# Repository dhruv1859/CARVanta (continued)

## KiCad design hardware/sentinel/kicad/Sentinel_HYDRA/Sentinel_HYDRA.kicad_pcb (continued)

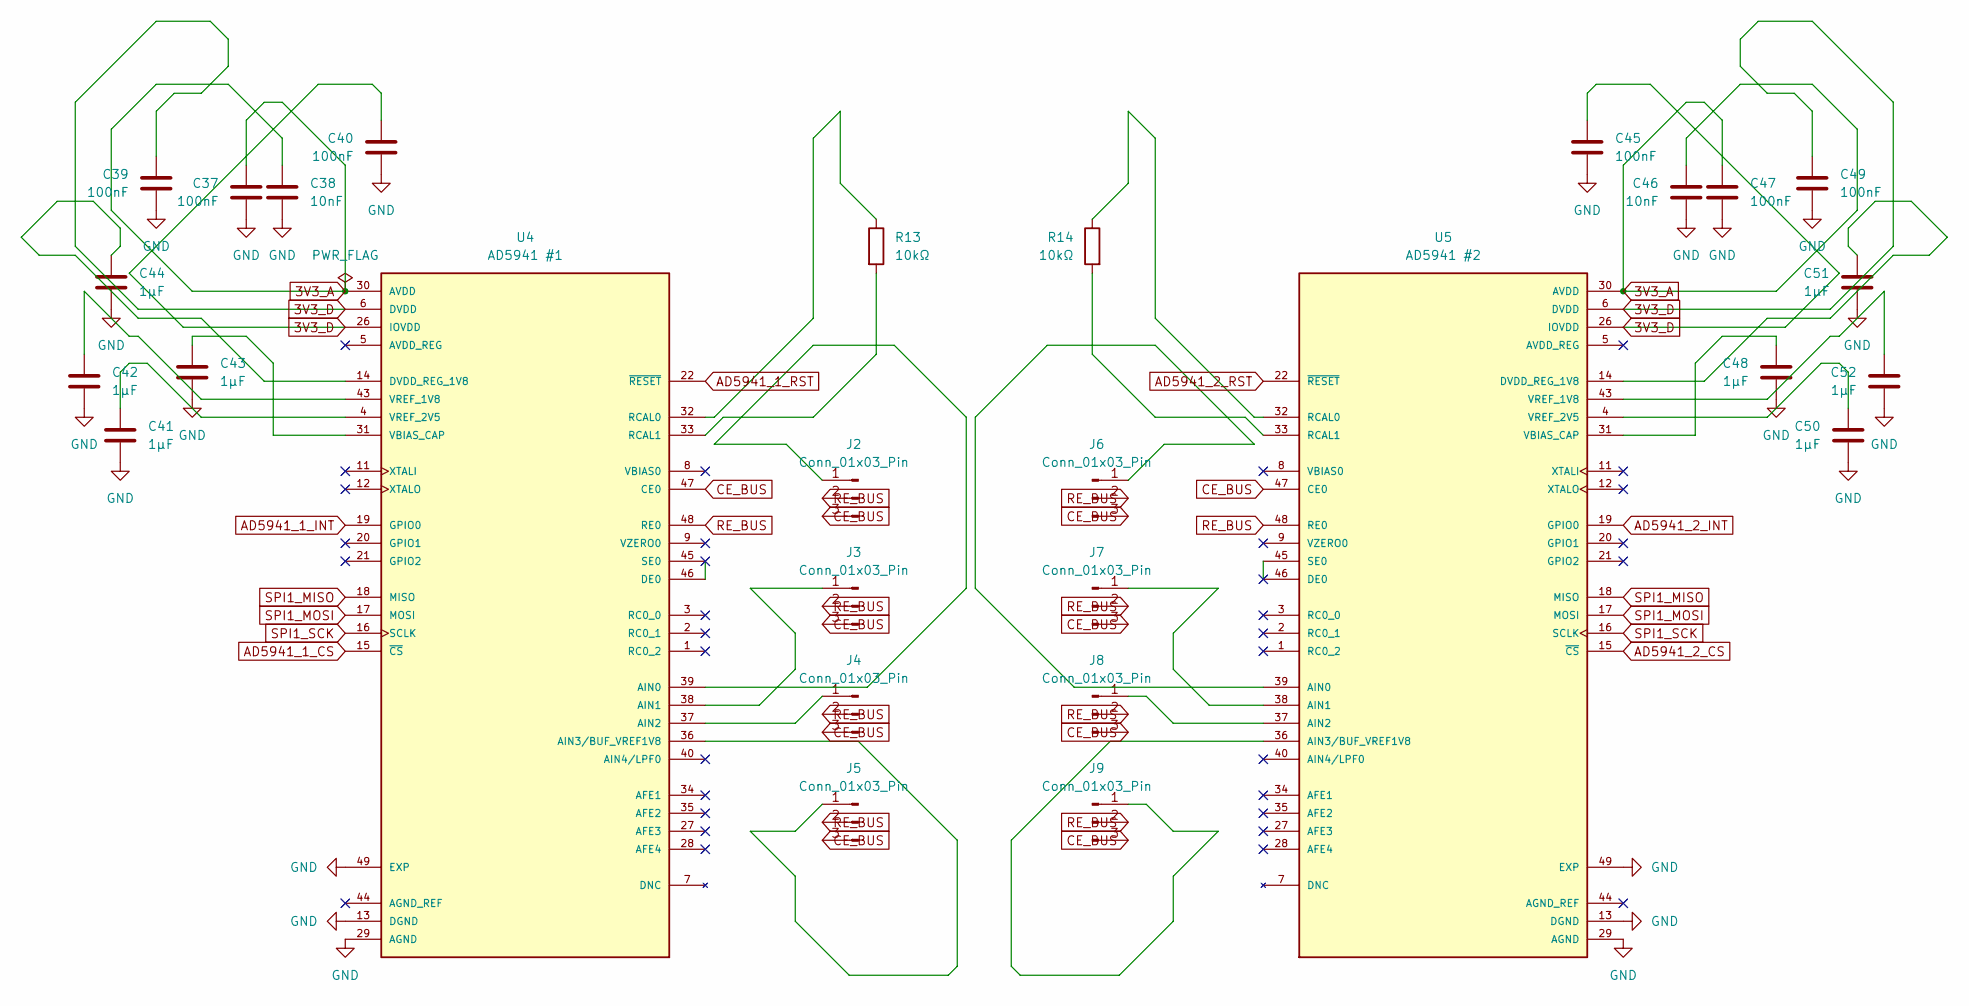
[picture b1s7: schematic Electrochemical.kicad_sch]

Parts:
C37, C39, C40, C45, C47, C49: 100nF; C_0402_1005Metric
C38, C46: 10nF; C_0402_1005Metric
C41, C42, C43, C44, C48, C50, C51, C52: 1µF; C_0402_1005Metric
J2, J3, J4, J5, J6, J7, J8, J9: Conn_01x03_Pin; Molex_PicoBlade_53047-0310_1x03_P1.25mm_Vertical
R13, R14: 10kΩ; R_0402_1005Metric
U4: AD5941 #1; QFN50P700X700X80-49N; PARTREV B
U5: AD5941 #2; QFN50P700X700X80-49N; PARTREV B

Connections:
3V3_A: C37.1, C38.1, C46.1, C47.1, U4.30 (AVDD), U4.41 (AVDD), U5.30 (AVDD), U5.41 (AVDD); also elsewhere on the board
3V3_D: C39.1, C40.1, C45.1, C49.1, U4.6 (DVDD), U4.26 (IOVDD), U5.6 (DVDD), U5.26 (IOVDD); also elsewhere on the board
+3V3: C37.2, C38.2, C39.2, C40.2, C41.2, C42.2, C43.2, C44.2, C45.2, C46.2, C47.2, C48.2, C49.2, C50.2, C51.2, C52.2, U4.13 (DGND), U4.23 (DGND), U4.25 (DGND), U4.29 (AGND), U4.42 (AGND), U4.49 (EXP), U5.13 (DGND), U5.23 (DGND), U5.25 (DGND), U5.29 (AGND), U5.42 (AGND), U5.49 (EXP); also elsewhere on the board
AD5941_1_CS: U4.15 (~CS); also elsewhere on the board
AD5941_1_INT: U4.19 (GPIO0); also elsewhere on the board
AD5941_1_RST: U4.22 (~RESET); also elsewhere on the board
AD5941_2_CS: U5.15 (~CS); also elsewhere on the board
AD5941_2_INT: U5.19 (GPIO0); also elsewhere on the board
AD5941_2_RST: U5.22 (~RESET); also elsewhere on the board
CE_BUS: J2.3, J3.3, J4.3, J5.3, J6.3, J7.3, J8.3, J9.3, U4.47 (CE0), U5.47 (CE0)
unnamed: J2.1, U4.39 (AIN0)
unnamed: J3.1, U4.38 (AIN1)
unnamed: J4.1, U4.37 (AIN2)
unnamed: J5.1, U4.36 (AIN3/BUF_VREF1V8)
unnamed: J6.1, U5.39 (AIN0)
unnamed: J7.1, U5.38 (AIN1)
unnamed: J8.1, U5.37 (AIN2)
unnamed: J9.1, U5.36 (AIN3/BUF_VREF1V8)
unnamed: C44.1, U4.14 (DVDD_REG_1V8)
unnamed: R13.1, U4.32 (RCAL0)
unnamed: R13.2, U4.33 (RCAL1)
unnamed: C43.1, U4.31 (VBIAS_CAP)
unnamed: C42.1, U4.43 (VREF_1V8)
unnamed: C41.1, U4.4 (VREF_2V5)
unnamed: C51.1, U5.14 (DVDD_REG_1V8)
unnamed: R14.1, U5.32 (RCAL0)
unnamed: R14.2, U5.33 (RCAL1)
unnamed: C48.1, U5.31 (VBIAS_CAP)
unnamed: C52.1, U5.43 (VREF_1V8)
unnamed: C50.1, U5.4 (VREF_2V5)
RE_BUS: J2.2, J3.2, J4.2, J5.2, J6.2, J7.2, J8.2, J9.2, U4.48 (RE0), U5.48 (RE0)
SPI1_MISO: U4.18 (MISO), U5.18 (MISO); also elsewhere on the board
SPI1_MOSI: U4.17 (MOSI), U5.17 (MOSI); also elsewhere on the board
SPI1_SCK: U4.16 (SCLK), U5.16 (SCLK); also elsewhere on the board

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
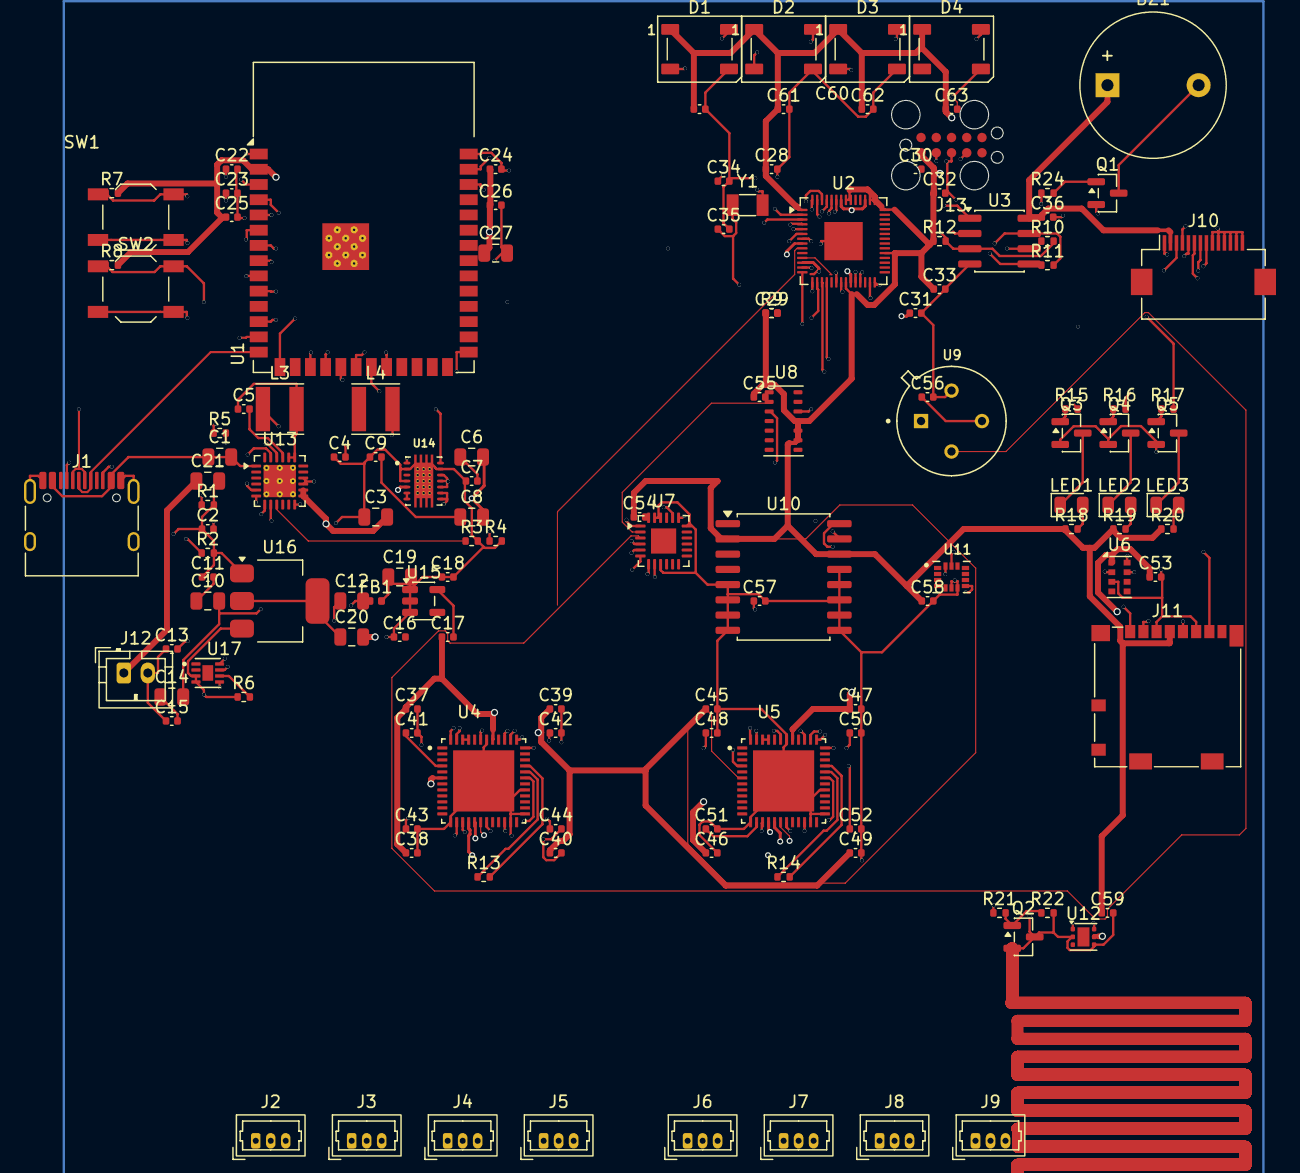
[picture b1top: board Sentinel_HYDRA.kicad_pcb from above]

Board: 6 copper layers, 135 parts (0 on the bottom side), 123 nets.

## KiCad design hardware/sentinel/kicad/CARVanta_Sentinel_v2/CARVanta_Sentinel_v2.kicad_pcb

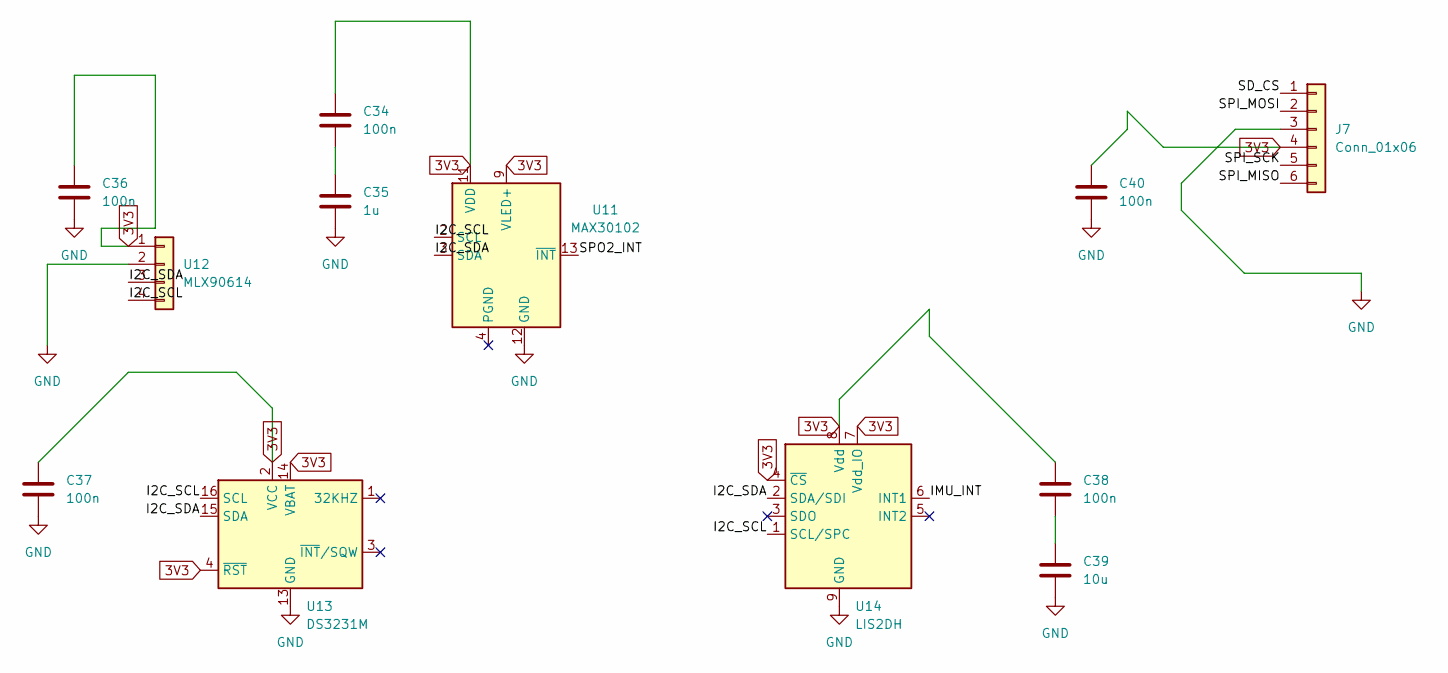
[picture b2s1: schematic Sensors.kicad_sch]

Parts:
C34, C36, C37, C38, C40: 100n; C_0805_2012Metric
C35: 1u; C_0805_2012Metric
C39: 10u; C_0805_2012Metric
J7: Conn_01x06; PinHeader_1x06_P2.54mm_Vertical
U11: MAX30102; Maxim_OLGA-14_3.3x5.6mm_P0.8mm
U12: MLX90614; TO-39-4
U13: DS3231M; SOIC-16W_7.5x10.3mm_P1.27mm
U14: LIS2DH; Bosch_LGA-14_3x2.5mm_P0.5mm

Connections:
3V3: C34.1, C35.2, C36.1, C36.2, C37.1, C37.2, C38.1, C39.2, C40.1, C40.2, J7.3, J7.4, U11.9 (VLED+), U11.10 (VLED+), U11.11 (VDD), U11.12 (GND), U12.1, U12.2, U13.2 (VCC), U13.4 (~RST), U13.5 (GND), U13.6 (GND), U13.7 (GND), U13.8 (GND), U13.9 (GND), U13.10 (GND), U13.11 (GND), U13.12 (GND), U13.13 (GND), U13.14 (VBAT), U14.4 (~CS), U14.7 (Vdd_IO), U14.8 (Vdd), U14.9 (GND), U14.10 (GND), U14.11 (GND), U14.12 (GND), U14.13 (GND), U14.14 (GND); also elsewhere on the board
/Sensors/I2C_SCL: U11.2 (SCL), U12.4, U13.16 (SCL), U14.1 (SCL/SPC)
/Sensors/I2C_SDA: U11.3 (SDA), U12.3, U13.15 (SDA), U14.2 (SDA/SDI)
/Sensors/IMU_INT: U14.6 (INT1)
/Sensors/SD_CS: J7.1
/Sensors/SPI_MISO: J7.6
/Sensors/SPI_MOSI: J7.2
/Sensors/SPI_SCK: J7.5
/Sensors/SPO2_INT: U11.13 (~INT)
unnamed: C34.2, C35.1
unnamed: C38.2, C39.1

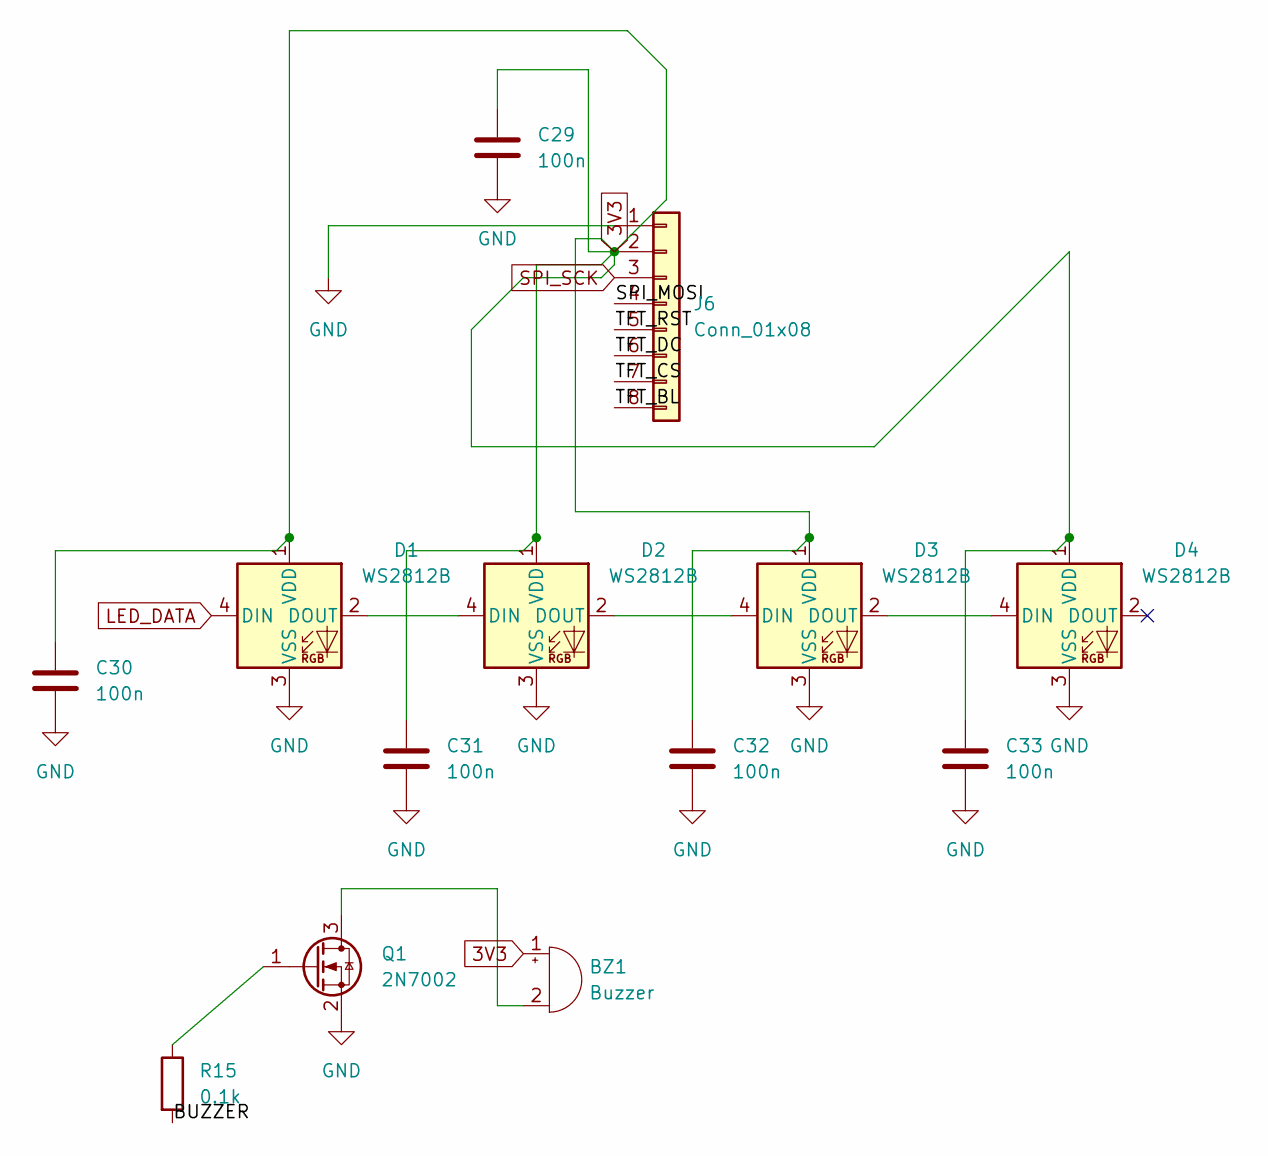
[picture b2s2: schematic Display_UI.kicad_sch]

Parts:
BZ1: Buzzer; Buzzer_12x9.5RM7.6
C29, C30, C31, C32, C33: 100n; C_0805_2012Metric
D1, D2, D3, D4: WS2812B; LED_WS2812B_PLCC4_5.0x5.0mm_P3.2mm
J6: Conn_01x08; PinHeader_1x08_P2.54mm_Vertical
Q1: 2N7002; SOT-23
R15: 0.1k; R_0402_1005Metric

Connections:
3V3: BZ1.1 (+), C29.1, C29.2, C30.1, C30.2, C31.1, C31.2, C32.1, C32.2, C33.1, C33.2, D1.1 (VDD), D1.3 (VSS), D2.1 (VDD), D2.3 (VSS), D3.1 (VDD), D3.3 (VSS), D4.1 (VDD), D4.3 (VSS), J6.1, J6.2, Q1.2 (S); also elsewhere on the board
/Display_UI/BUZZER: R15.2
/Display_UI/SPI_MOSI: J6.4
/Display_UI/TFT_BL: J6.8
/Display_UI/TFT_CS: J6.7
/Display_UI/TFT_DC: J6.6
/Display_UI/TFT_RST: J6.5
LED_DATA: D1.4 (DIN); also elsewhere on the board
unnamed: BZ1.2 (-), Q1.3 (D)
unnamed: D1.2 (DOUT), D2.4 (DIN)
unnamed: D2.2 (DOUT), D3.4 (DIN)
unnamed: D3.2 (DOUT), D4.4 (DIN)
unnamed: Q1.1 (G), R15.1
SPI_SCK: J6.3; also elsewhere on the board

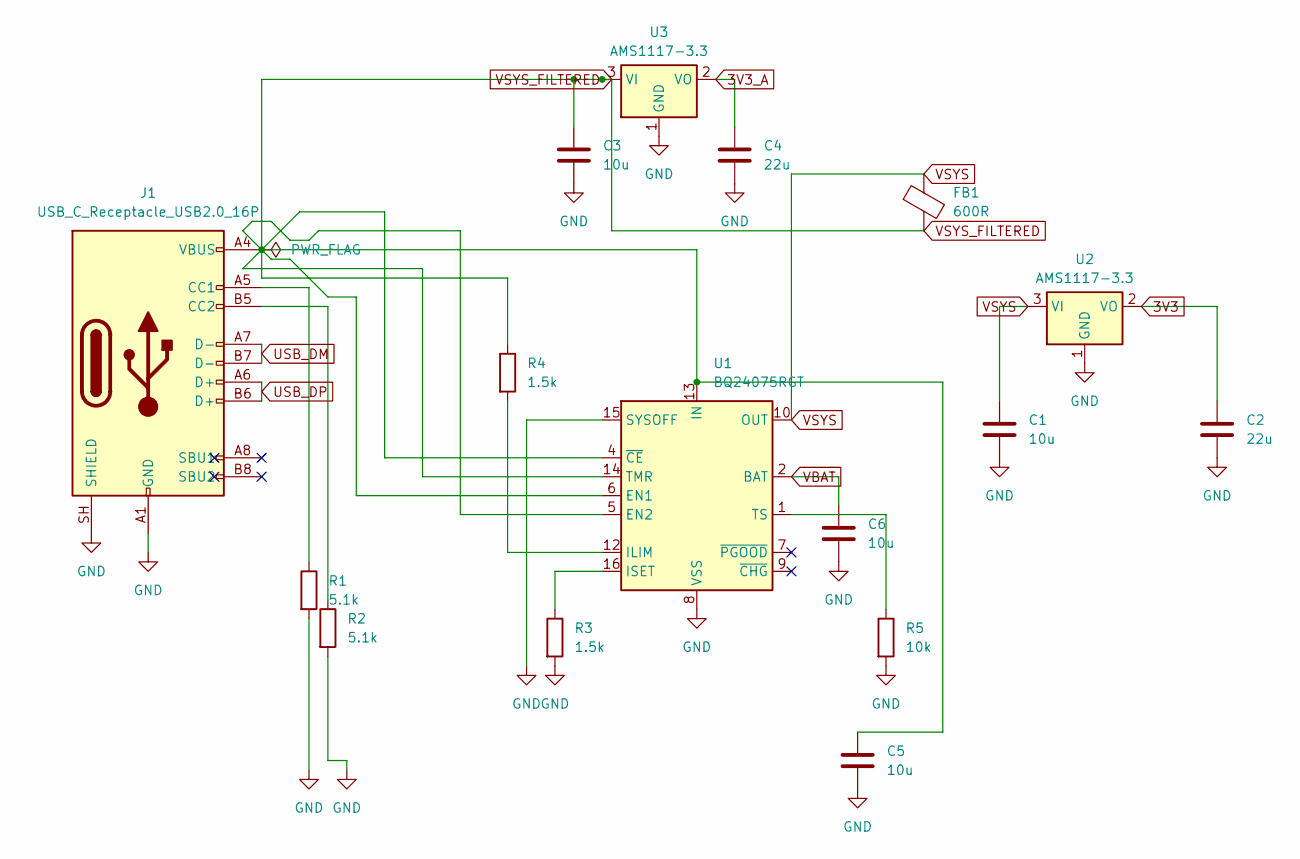
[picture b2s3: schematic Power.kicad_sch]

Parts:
C1, C3, C5, C6: 10u; C_0805_2012Metric
C2, C4: 22u; C_0805_2012Metric
FB1: 600R; L_0402_1005Metric
J1: USB_C_Receptacle_USB2.0_16P; USB_C_Receptacle_HCTL_HC-TYPE-C-16P-01A
R1, R2: 5.1k; R_0402_1005Metric
R3, R4: 1.5k; R_0402_1005Metric
R5: 10k; R_0402_1005Metric
U1: BQ24075RGT; VQFN-16-1EP_3x3mm_P0.5mm_EP1.8x1.8mm
U2, U3: AMS1117-3.3; SOT-223-3_TabPin2

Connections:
3V3: C1.2, C2.1, C2.2, C3.2, C4.2, C5.2, C6.2, J1.A1 (GND), J1.A12 (GND), J1.B1 (GND), J1.B12 (GND), J1.SH (SHIELD), R1.2, R2.2, R3.2, R5.2, U1.8 (VSS), U1.15 (SYSOFF), U1.17 (VSS), U2.1 (GND), U2.2 (VO), U3.1 (GND); also elsewhere on the board
3V3_A: C4.1, U3.2 (VO); also elsewhere on the board
unnamed: J1.A5 (CC1), R1.1
unnamed: J1.B5 (CC2), R2.1
unnamed: R4.2, U1.12 (ILIM)
unnamed: R3.1, U1.16 (ISET)
unnamed: R5.1, U1.1 (TS)
USB_DM: J1.A7 (D-), J1.B7 (D-); also elsewhere on the board
USB_DP: J1.A6 (D+), J1.B6 (D+); also elsewhere on the board
VBAT: C6.1, U1.2 (BAT), U1.3 (BAT); also elsewhere on the board
VSYS: C1.1, FB1.1, U1.10 (OUT), U1.11 (OUT), U2.3 (VI)
VSYS_FILTERED: C3.1, C5.1, FB1.2, J1.A4 (VBUS), J1.A9 (VBUS), J1.B4 (VBUS), J1.B9 (VBUS), R4.1, U1.4 (~CE), U1.5 (EN2), U1.6 (EN1), U1.13 (IN), U1.14 (TMR), U3.3 (VI)

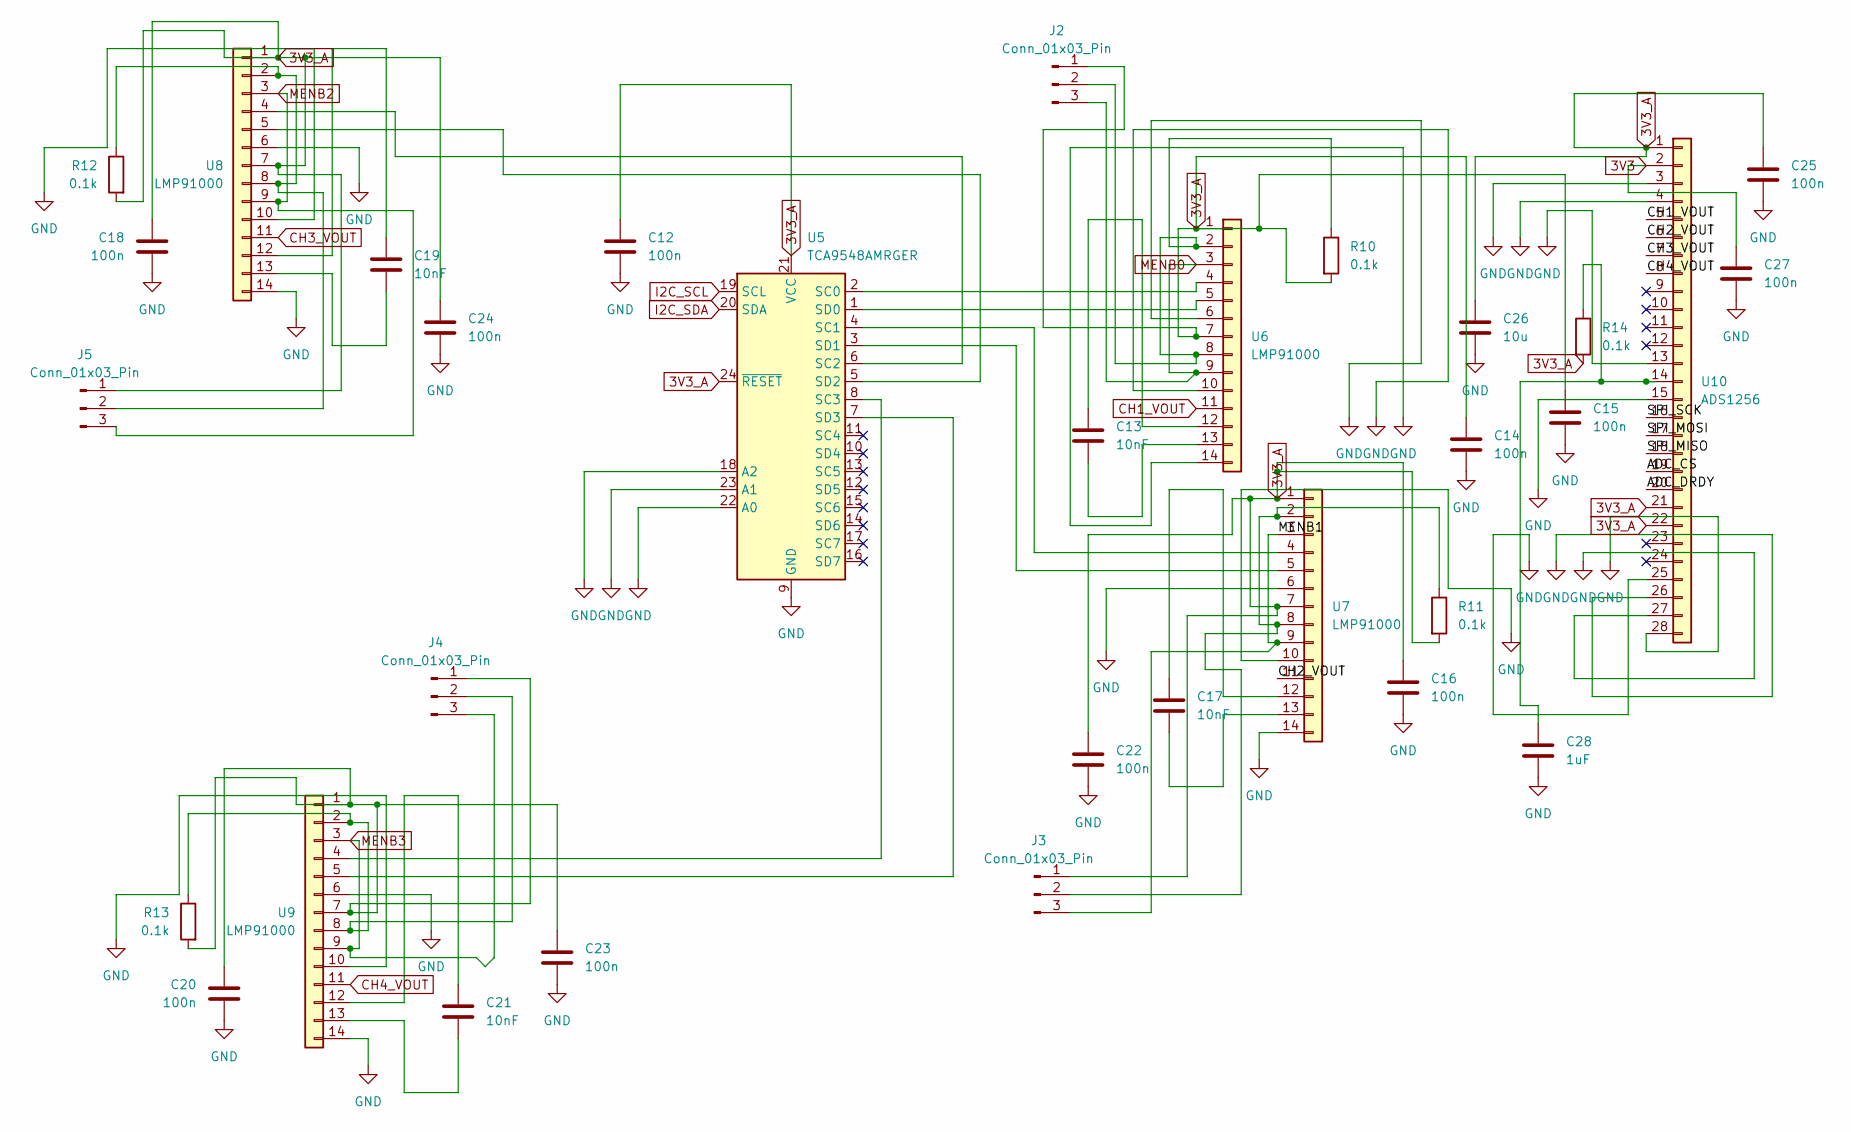
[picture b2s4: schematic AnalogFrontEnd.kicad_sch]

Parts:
C12, C14, C15, C16, C18, C20, C22, C23, C24, C25, C27: 100n; C_0805_2012Metric
C13, C17, C19, C21: 10nF; C_0805_2012Metric
C26: 10u; C_0805_2012Metric
C28: 1uF; C_0805_2012Metric
J2, J3, J4, J5: Conn_01x03_Pin; PinHeader_1x03_P2.54mm_Vertical
R10, R11, R12, R13, R14: 0.1k; R_0402_1005Metric
U5: TCA9548AMRGER; TSSOP-24_4.4x7.8mm_P0.65mm
U6, U7, U8, U9: LMP91000; TSSOP-14_4.4x5mm_P0.65mm
U10: ADS1256; TSSOP-28_4.4x9.7mm_P0.65mm

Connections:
3V3: C12.2, C14.2, C15.2, C16.2, C18.2, C20.2, C22.2, C23.2, C24.2, C25.2, C26.2, C27.1, C27.2, C28.2, U5.9 (GND), U5.18 (A2), U5.22 (A0), U5.23 (A1), U6.6, U6.10, U6.14, U7.6, U7.10, U7.14, U8.6, U8.10, U8.14, U9.6, U9.10, U9.14, U10.2, U10.3, U10.4, U10.13, U10.15, U10.25, U10.26, U10.27, U10.28; also elsewhere on the board
3V3_A: C12.1, C14.1, C15.1, C16.1, C18.1, C22.1, C24.1, C25.1, C26.1, J2.1, J3.1, J5.1, R10.2, R11.2, R12.2, R14.2, U5.21 (VCC), U5.24 (~RESET), U6.1, U6.7, U7.1, U7.7, U8.1, U8.7, U10.1, U10.21, U10.22; also elsewhere on the board
/AnalogFrontEnd/ADC_CS: U10.19
/AnalogFrontEnd/ADC_DRDY: U10.20
/AnalogFrontEnd/CH2_VOUT: U7.11, U10.6
/AnalogFrontEnd/MENB1: J3.3, U7.3, U7.9
/AnalogFrontEnd/SPI_MISO: U10.18
/AnalogFrontEnd/SPI_MOSI: U10.17
/AnalogFrontEnd/SPI_SCK: U10.16
CH1_VOUT: U6.11, U10.5
CH3_VOUT: U8.11, U10.7
CH4_VOUT: U9.11, U10.8
I2C_SCL: U5.19 (SCL); also elsewhere on the board
I2C_SDA: U5.20 (SDA); also elsewhere on the board
MENB0: J2.3, U6.3, U6.9; also elsewhere on the board
MENB2: J5.3, U8.3, U8.9; also elsewhere on the board
MENB3: J4.3, U9.3, U9.9; also elsewhere on the board
unnamed: J2.2, R10.1, U6.2, U6.8
unnamed: J3.2, R11.1, U7.2, U7.8
unnamed: C20.1, C23.1, J4.1, R13.2, U9.1, U9.7
unnamed: J4.2, R13.1, U9.2, U9.8
unnamed: J5.2, R12.1, U8.2, U8.8
unnamed: U5.2 (SC0), U6.4
unnamed: U5.4 (SC1), U7.4
unnamed: U5.6 (SC2), U8.4
unnamed: U5.8 (SC3), U9.4
unnamed: U5.1 (SD0), U6.5
unnamed: U5.3 (SD1), U7.5
unnamed: U5.5 (SD2), U8.5
unnamed: U5.7 (SD3), U9.5
unnamed: C13.1, U6.12
unnamed: C13.2, U6.13
unnamed: C17.1, U7.12
unnamed: C17.2, U7.13
unnamed: C19.1, U8.12
unnamed: C19.2, U8.13
unnamed: C21.1, U9.12
unnamed: C21.2, U9.13
unnamed: C28.1, R14.1, U10.14

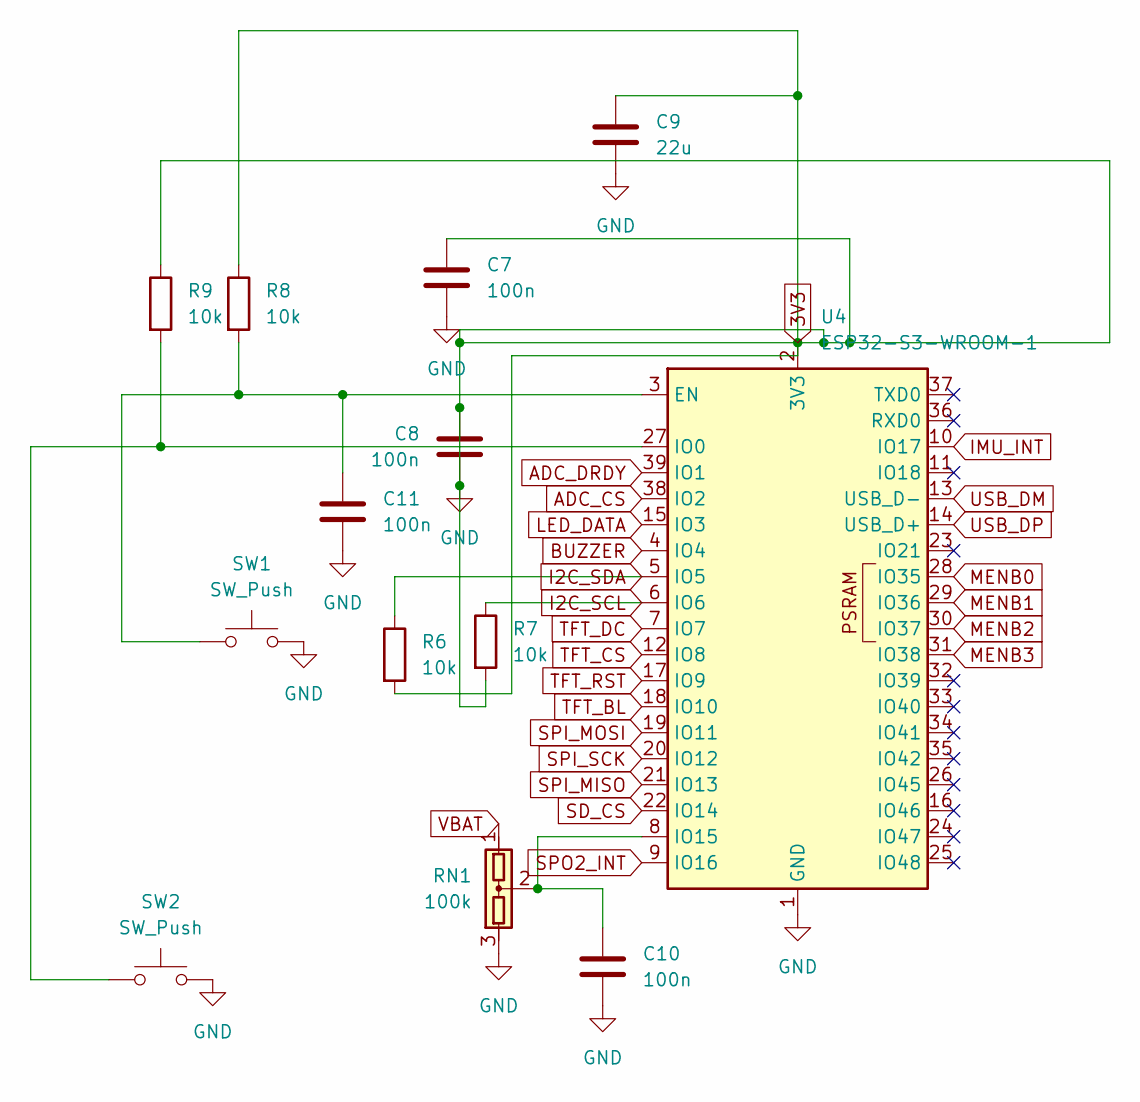
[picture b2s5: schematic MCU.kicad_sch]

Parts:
C7, C8, C10, C11: 100n; C_0805_2012Metric
C9: 22u; C_0805_2012Metric
R6, R7, R8, R9: 10k; R_0402_1005Metric
RN1: 100k; R_Array_Convex_2x0402
SW1, SW2: SW_Push; SW_SPST_PTS645Sx43SMTR92
U4: ESP32-S3-WROOM-1

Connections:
3V3: C7.1, C7.2, C8.1, C8.2, C9.1, C9.2, C10.2, C11.2, R6.2, R7.2, R8.1, R9.1, RN1.3, SW1.2, SW2.2, U4.1 (GND), U4.2 (3V3), U4.40 (GND), U4.41 (GND); also elsewhere on the board
ADC_CS: U4.38 (IO2)
ADC_DRDY: U4.39 (IO1)
BUZZER: U4.4 (IO4)
I2C_SCL: R7.1, U4.6 (IO6); also elsewhere on the board
I2C_SDA: R6.1, U4.5 (IO5); also elsewhere on the board
IMU_INT: U4.10 (IO17)
LED_DATA: U4.15 (IO3); also elsewhere on the board
MENB0: U4.28 (IO35); also elsewhere on the board
MENB1: U4.29 (IO36)
MENB2: U4.30 (IO37); also elsewhere on the board
MENB3: U4.31 (IO38); also elsewhere on the board
unnamed: C11.1, R8.2, SW1.1, U4.3 (EN)
unnamed: R9.2, SW2.1, U4.27 (IO0)
unnamed: C10.1, RN1.2, U4.8 (IO15)
SD_CS: U4.22 (IO14)
SPI_MISO: U4.21 (IO13)
SPI_MOSI: U4.19 (IO11)
SPI_SCK: U4.20 (IO12); also elsewhere on the board
SPO2_INT: U4.9 (IO16)
TFT_BL: U4.18 (IO10)
TFT_CS: U4.12 (IO8)
TFT_DC: U4.7 (IO7)
TFT_RST: U4.17 (IO9)
USB_DM: U4.13 (USB_D-); also elsewhere on the board
USB_DP: U4.14 (USB_D+); also elsewhere on the board
VBAT: RN1.1; also elsewhere on the board

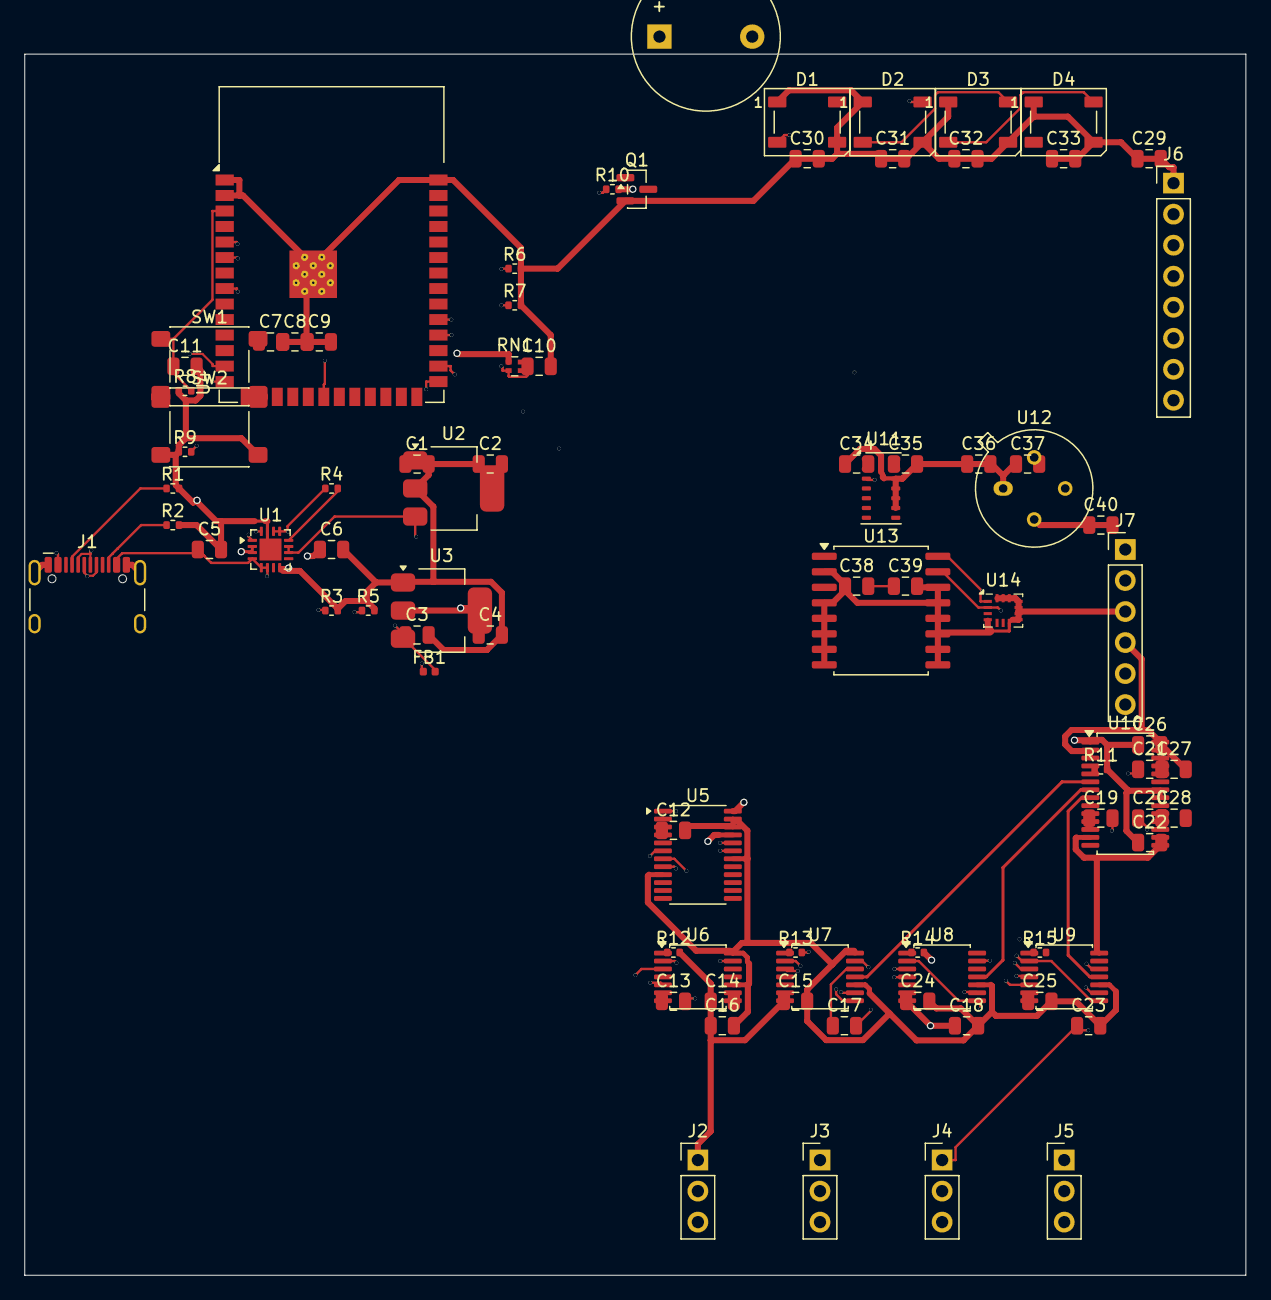
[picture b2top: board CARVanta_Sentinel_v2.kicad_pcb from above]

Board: 6 copper layers, 100.0 x 100.0 mm, 86 parts (0 on the bottom side), 58 nets.

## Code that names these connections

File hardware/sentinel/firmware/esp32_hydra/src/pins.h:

/*
 * CARVanta Sentinel HYDRA — ESP32-S3 Pin Definitions
 * Matches KiCad schematic: HYDRA_WALKTHROUGH_PART1.md
 * Sheet 2: ESP32 Pin Map
 */

#pragma once

// ─── UART to RP2040 ──────────────────────────────────────
#define PIN_UART_TX         1   // GPIO1 → RP2040 GPIO0 (RX)
#define PIN_UART_RX         2   // GPIO2 ← RP2040 GPIO1 (TX)

// ─── I2C Main Bus (→ TCA9548A Mux) ──────────────────────
#define PIN_I2C_SDA         5   // GPIO5
#define PIN_I2C_SCL         6   // GPIO6

// ─── SPI0 (TFT Display + SD Card) ───────────────────────
#define PIN_SPI0_MOSI       11  // GPIO11
#define PIN_SPI0_SCK        12  // GPIO12
#define PIN_SPI0_MISO       13  // GPIO13
#define PIN_TFT_CS          8   // GPIO8
#define PIN_TFT_DC          7   // GPIO7
#define PIN_TFT_RST         9   // GPIO9
#define PIN_TFT_BL          10  // GPIO10
#define PIN_SD_CS           14  // GPIO14

// ─── UI: LEDs + Buzzer ──────────────────────────────────
#define PIN_LED_DATA        3   // GPIO3 → WS2812B D1 DIN
#define PIN_BUZZER          4   // GPIO4 → Q1 gate (buzzer driver)
#define NUM_WS2812B_LEDS    4   // D1–D4

// ─── Status Inputs ──────────────────────────────────────
#define PIN_CHG_INT         15  // GPIO15 ← BQ25895 INT (charge status)
#define PIN_BATT_ALT        16  // GPIO16 ← MAX17048 ALT (low battery)
#define PIN_PG_3V3          17  // GPIO17 ← TPS63020 PG (power good)

// ─── USB (Hardware-fixed, cannot remap) ──────────────────
#define PIN_USB_DM          19  // GPIO19 — USB D−
#define PIN_USB_DP          20  // GPIO20 — USB D+

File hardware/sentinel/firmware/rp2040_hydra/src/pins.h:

/*
 * CARVanta Sentinel HYDRA — RP2040 Pin Definitions
 * Matches KiCad schematic: HYDRA_WALKTHROUGH_PART1.md
 * Sheet 3: RP2040 Pin Map
 */

#pragma once

// ─── UART to ESP32 ───────────────────────────────────────
#define PIN_UART_RX         0   // GPIO0 ← ESP32 GPIO1 (TX)
#define PIN_UART_TX         1   // GPIO1 → ESP32 GPIO2 (RX)

// ─── SPI1 — AD5941 Bus ──────────────────────────────────
#define PIN_SPI1_SCK        6   // GPIO6
#define PIN_SPI1_MOSI       7   // GPIO7
#define PIN_SPI1_MISO       8   // GPIO8
#define PIN_AD5941_1_CS     2   // GPIO2  — AFE #1 chip select
#define PIN_AD5941_1_RST    3   // GPIO3  — AFE #1 reset
#define PIN_AD5941_2_CS     4   // GPIO4  — AFE #2 chip select
#define PIN_AD5941_2_RST    5   // GPIO5  — AFE #2 reset
#define PIN_AD5941_1_INT    9   // GPIO9  — AFE #1 interrupt
#define PIN_AD5941_2_INT    10  // GPIO10 — AFE #2 interrupt

// ─── I2C1 — AS7341 + TMP117 ────────────────────────────
#define PIN_I2C1_SDA        12  // GPIO12  (Wire1)
#define PIN_I2C1_SCL        13  // GPIO13  (Wire1)

// ─── Heater PWM ─────────────────────────────────────────
#define PIN_HEATER_PWM      14  // GPIO14 → AO3400 gate

// ─── Excitation LEDs ────────────────────────────────────
#define PIN_UV_LED_EN       15  // GPIO15 → Q3 gate (UV 365nm)
#define PIN_BLUE_LED_EN     16  // GPIO16 → Q4 gate (Blue 470nm)
#define PIN_WHITE_LED_EN    17  // GPIO17 → Q5 gate (White)

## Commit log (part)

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2026-03-23 git push -u origin main --forceInitial commit
2026-03-23 Bump actions/setup-python from 5 to 6
    Bumps [actions/setup-python](https://github.com/actions/setup-python) from 5 to 6.
    - [Release notes](https://github.com/actions/setup-python/releases)
    - [Commits](https://github.com/actions/setup-python/compare/v5...v6)
    ---
    updated-dependencies:
    - dependency-name: actions/setup-python
2026-03-23 Bump actions/setup-node from 4 to 6
    Bumps [actions/setup-node](https://github.com/actions/setup-node) from 4 to 6.
    - [Release notes](https://github.com/actions/setup-node/releases)
    - [Commits](https://github.com/actions/setup-node/compare/v4...v6)
    ---
    updated-dependencies:
    - dependency-name: actions/setup-node
2026-03-23 Removed sensitive files
2026-03-23 Ignore env and secrets
2026-03-23 Removed failing GitHub workflows
2026-03-23 Create security policy document
    Added a security policy for reporting vulnerabilities.
2026-03-23 Add initial Code of Conduct document
2026-03-23 Add Apache License 2.0
    Added the Apache License 2.0 to the project.
2026-03-26 restore: Recovered deleted .github/workflows and docker-compose.dev.yml
2026-03-26 chore: stage pending changes
2026-03-26 security: remove hardcoded secrets, use env_file in docker-compose
    - auth.py: removed hardcoded JWT_SECRET and PASSWORD_SALT fallbacks
    - docker-compose.dev.yml: replaced inline keys with env_file reference
    - .env.example: added JWT_SECRET, PASSWORD_SALT, SMTP placeholders
2026-03-26 fix: auto-verify accounts in dev mode (SMTP blocked by network)
2026-03-26 fix: auto-login on registration in dev mode - skip verification screen
2026-03-27 chore(deps): bump brace-expansion in /frontend-react
    Bumps and [brace-expansion](https://github.com/juliangruber/brace-expansion). These dependencies needed to be updated together.
    Updates `brace-expansion` from 1.1.12 to 1.1.13
    - [Release notes](https://github.com/juliangruber/brace-expansion/releases)
    - [Commits](https://github.com/juliangruber/brace-expansion/compare/v1.1.12...v1.1.13)
    Updates `brace-expansion` from 5.0.4 to 5.0.5
    - [Release notes](https://github.com/juliangruber/brace-expansion/releases)
2026-03-30 chore(deps): bump actions/checkout from 4 to 6
    Bumps [actions/checkout](https://github.com/actions/checkout) from 4 to 6.
    - [Release notes](https://github.com/actions/checkout/releases)
    - [Changelog](https://github.com/actions/checkout/blob/main/CHANGELOG.md)
    - [Commits](https://github.com/actions/checkout/compare/v4...v6)
    ---
    updated-dependencies:
2026-04-07 chore(deps-dev): bump vite from 7.3.1 to 7.3.2 in /frontend-react
    Bumps [vite](https://github.com/vitejs/vite/tree/HEAD/packages/vite) from 7.3.1 to 7.3.2.
    - [Release notes](https://github.com/vitejs/vite/releases)
    - [Changelog](https://github.com/vitejs/vite/blob/v7.3.2/packages/vite/CHANGELOG.md)
    - [Commits](https://github.com/vitejs/vite/commits/v7.3.2/packages/vite)
    ---
    updated-dependencies:
2026-04-13 chore(deps): bump softprops/action-gh-release from 2 to 3
    Bumps [softprops/action-gh-release](https://github.com/softprops/action-gh-release) from 2 to 3.
    - [Release notes](https://github.com/softprops/action-gh-release/releases)
    - [Changelog](https://github.com/softprops/action-gh-release/blob/master/CHANGELOG.md)
    - [Commits](https://github.com/softprops/action-gh-release/compare/v2...v3)
    ---
    updated-dependencies:
2026-04-24 Add mobile responsive layout, Vercel + Render deployment configs
2026-04-24 chore(deps): update alembic requirement from >=1.12.0 to >=1.18.4
    Updates the requirements on [alembic](https://github.com/sqlalchemy/alembic) to permit the latest version.
    - [Release notes](https://github.com/sqlalchemy/alembic/releases)
    - [Changelog](https://github.com/sqlalchemy/alembic/blob/main/CHANGES)
    - [Commits](https://github.com/sqlalchemy/alembic/commits)
    ---
    updated-dependencies:
2026-04-24 chore(deps): update pytest requirement from >=7.4.0 to >=9.0.3
    Updates the requirements on [pytest](https://github.com/pytest-dev/pytest) to permit the latest version.
    - [Release notes](https://github.com/pytest-dev/pytest/releases)
    - [Changelog](https://github.com/pytest-dev/pytest/blob/main/CHANGELOG.rst)
    - [Commits](https://github.com/pytest-dev/pytest/compare/7.4.0...9.0.3)
    ---
    updated-dependencies:
2026-04-24 chore(deps): update reportlab requirement from >=4.0.0 to >=4.4.10
    Updates the requirements on [reportlab](https://www.reportlab.com/) to permit the latest version.
    ---
    updated-dependencies:
    - dependency-name: reportlab
    dependency-version: 4.4.10
    dependency-type: direct:production
2026-04-24 chore(deps-dev): bump typescript from 5.9.3 to 6.0.3 in /frontend-react
    Bumps [typescript](https://github.com/microsoft/TypeScript) from 5.9.3 to 6.0.3.
    - [Release notes](https://github.com/microsoft/TypeScript/releases)
    - [Commits](https://github.com/microsoft/TypeScript/compare/v5.9.3...v6.0.3)
    ---
    updated-dependencies:
    - dependency-name: typescript
2026-04-24 chore(deps-dev): bump @vitejs/plugin-react in /frontend-react
    Bumps [@vitejs/plugin-react](https://github.com/vitejs/vite-plugin-react/tree/HEAD/packages/plugin-react) from 5.1.4 to 6.0.1.
    - [Release notes](https://github.com/vitejs/vite-plugin-react/releases)
    - [Changelog](https://github.com/vitejs/vite-plugin-react/blob/main/packages/plugin-react/CHANGELOG.md)
    - [Commits](https://github.com/vitejs/vite-plugin-react/commits/plugin-react@6.0.1/packages/plugin-react)
    ---
    updated-dependencies:
2026-04-24 chore(deps): bump react-dom from 19.2.4 to 19.2.5 in /frontend-react
    Bumps [react-dom](https://github.com/facebook/react/tree/HEAD/packages/react-dom) from 19.2.4 to 19.2.5.
    - [Release notes](https://github.com/facebook/react/releases)
    - [Changelog](https://github.com/facebook/react/blob/main/CHANGELOG.md)
    - [Commits](https://github.com/facebook/react/commits/v19.2.5/packages/react-dom)
    ---
    updated-dependencies:
2026-04-24 chore(deps): bump axios from 1.13.6 to 1.15.2 in /frontend-react
    Bumps [axios](https://github.com/axios/axios) from 1.13.6 to 1.15.2.
    - [Release notes](https://github.com/axios/axios/releases)
    - [Changelog](https://github.com/axios/axios/blob/v1.x/CHANGELOG.md)
    - [Commits](https://github.com/axios/axios/compare/v1.13.6...v1.15.2)
    ---
    updated-dependencies:
2026-04-24 chore(deps-dev): bump globals from 16.5.0 to 17.5.0 in /frontend-react
    Bumps [globals](https://github.com/sindresorhus/globals) from 16.5.0 to 17.5.0.
    - [Release notes](https://github.com/sindresorhus/globals/releases)
    - [Commits](https://github.com/sindresorhus/globals/compare/v16.5.0...v17.5.0)
    ---
    updated-dependencies:
    - dependency-name: globals
2026-04-24 chore(deps-dev): bump eslint-plugin-react-refresh in /frontend-react
    Bumps [eslint-plugin-react-refresh](https://github.com/ArnaudBarre/eslint-plugin-react-refresh) from 0.4.26 to 0.5.2.
    - [Release notes](https://github.com/ArnaudBarre/eslint-plugin-react-refresh/releases)
    - [Changelog](https://github.com/ArnaudBarre/eslint-plugin-react-refresh/blob/main/CHANGELOG.md)
    - [Commits](https://github.com/ArnaudBarre/eslint-plugin-react-refresh/compare/v0.4.26...v0.5.2)
    ---
    updated-dependencies:
2026-04-24 Use nixpacks for Railway: lighter deps, no Docker
2026-04-24 Add data cache files for faster API startup on Railway
2026-04-25 Add Deep Learning Suite: GNN, Transformer, MLP, VAE, LSTM — 5 neural networks in pure NumPy with API + frontend
2026-04-25 Wire LLM ai_insight display to all major frontend pages: SingleAnalysis, Comparison, DigitalTwin, NLPSearch, ResearchCopilot + add ai_insight to batch_score API
2026-04-25 Railway deployment config + comprehensive README + deploy requirements with xgboost/scipy/httpx
2026-04-25 Disable render.yaml blueprint to prevent duplicate Railway service
2026-04-25 fix: bootstrap pip via venv in nixpacks.toml install phase
2026-04-25 fix: use pip binary directly in nixpacks install phase
2026-06-01 Bump gitleaks/gitleaks-action from 2 to 3
    Bumps [gitleaks/gitleaks-action](https://github.com/gitleaks/gitleaks-action) from 2 to 3.
    - [Release notes](https://github.com/gitleaks/gitleaks-action/releases)
    - [Commits](https://github.com/gitleaks/gitleaks-action/compare/v2...v3)
    ---
    updated-dependencies:
    - dependency-name: gitleaks/gitleaks-action
2026-06-05 Bump axios from 1.13.6 to 1.16.0 in /frontend-react
    Bumps [axios](https://github.com/axios/axios) from 1.13.6 to 1.16.0.
    - [Release notes](https://github.com/axios/axios/releases)
    - [Changelog](https://github.com/axios/axios/blob/v1.x/CHANGELOG.md)
    - [Commits](https://github.com/axios/axios/compare/v1.13.6...v1.16.0)
    ---
    updated-dependencies:
2026-06-07 Bump react-router and react-router-dom in /frontend-react
    Bumps [react-router](https://github.com/remix-run/react-router/tree/HEAD/packages/react-router) to 7.17.0 and updates ancestor dependency [react-router-dom](https://github.com/remix-run/react-router/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
    Updates `react-router` from 7.13.1 to 7.17.0
    - [Release notes](https://github.com/remix-run/react-router/releases)
    - [Changelog](https://github.com/remix-run/react-router/blob/main/packages/react-router/CHANGELOG.md)
    - [Commits](https://github.com/remix-run/react-router/commits/react-router@7.17.0/packages/react-router)
    Updates `react-router-dom` from
2026-06-14 feat: complete Sentinel HYDRA firmware rewrite + Render deployment config
    - ESP32-S3: 34 firmware files (sensors, comms, UI, storage, system)
    - RP2040: 16 firmware files (AD5941 AFE, AS7341 spectral, TMP117, PID heater)
    - FreeRTOS dual-core architecture with CRC8 UART protocol
    - Updated PITCH.md with current project metrics (117K lines)
    - Added Render deployment config (render.yaml)
    - Updated vercel.json for backend proxy
2026-06-14 fix: point frontend API proxy to Render backend
2026-06-14 trigger: Vercel redeploy from GitHub
2026-06-15 feat: add Sentinel HYDRA Gerber manufacturing package + documentation overhaul
    - Generate production Gerbers (6-layer, all copper + mask + silk + paste + edge)
    - Generate Excellon drill files (PTH + NPTH separated)
    - Create manufacturing-ready ZIP for JLCPCB/PCBWay
    - Rewrite README with hardware section and updated architecture
    - Full Contributor Covenant v2.1 Code of Conduct
    - Comprehensive contributing guide (software + hardware + firmware)
2026-06-16 chore(deps): bump react-router and react-router-dom in /frontend-react
    Bumps [react-router](https://github.com/remix-run/react-router/tree/HEAD/packages/react-router) to 7.18.0 and updates ancestor dependency [react-router-dom](https://github.com/remix-run/react-router/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
    Updates `react-router` from 7.13.1 to 7.18.0
    - [Release notes](https://github.com/remix-run/react-router/releases)
    - [Changelog](https://github.com/remix-run/react-router/blob/main/packages/react-router/CHANGELOG.md)
    - [Commits](https://github.com/remix-run/react-router/commits/react-router@7.18.0/packages/react-router)
    Updates `react-rout
